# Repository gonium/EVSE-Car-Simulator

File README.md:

# EVSE-Car-Simulator

A simple car simulator PCB for testing EVSE, implements DIN EN 61851 and
J1772. This repository contains:

1. The hardware design files (KICAD)
2. The documentation for the car simulator.

Please see [https://evsim.gonium.net](https://evsim.gonium.net) for more
information.

# License

This project is (c) 2017 Mathias Dalheimer and available under the MIT
license. In short:

Permissions:
* Commercial use ok
* Modification ok
* Distribution ok
* Private use ok

Limitations:
* no liability
* no warranty

Conditions:
* keep license and copyright notice

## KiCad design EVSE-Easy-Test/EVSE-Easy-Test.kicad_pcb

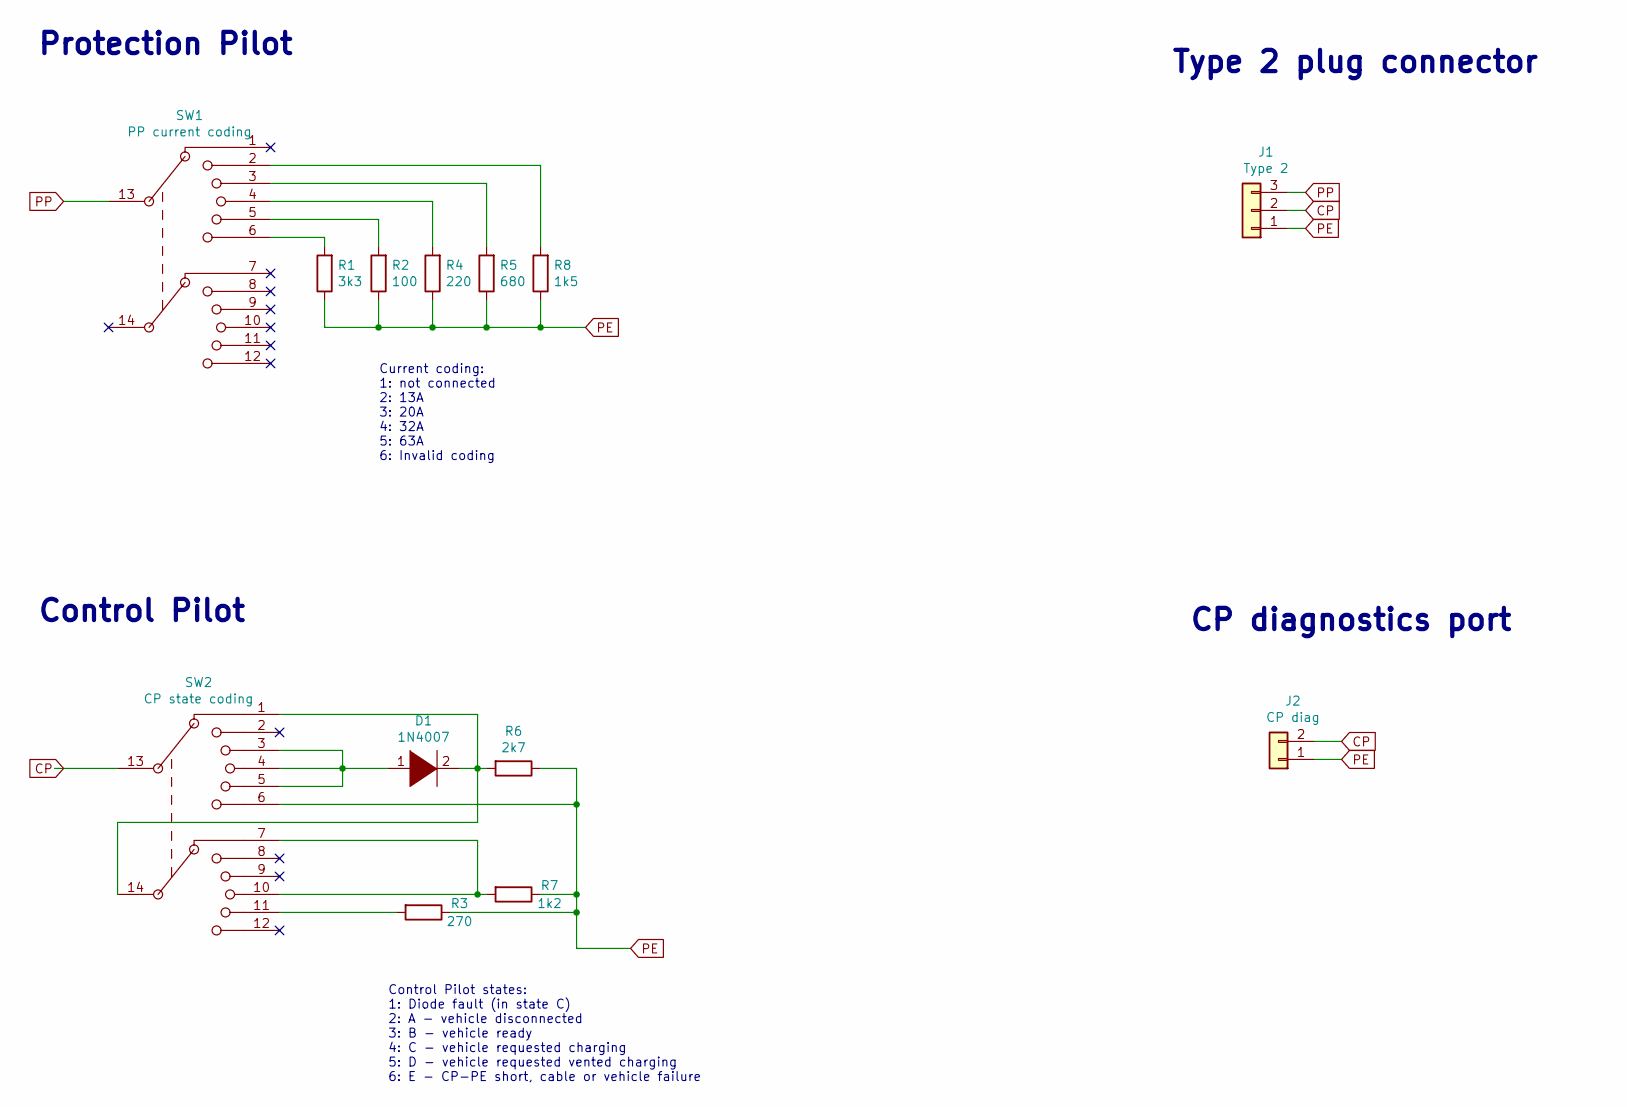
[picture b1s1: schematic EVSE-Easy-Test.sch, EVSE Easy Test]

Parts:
D1: 1N4007; D_DO-41_SOD81_P7.62mm_Horizontal
J1: Type 2; RIACon175_3poles_AKL175-03
J2: CP diag; Pin_Header_Straight_1x02_Pitch2.54mm
R1: 3k3; R_Axial_DIN0204_L3.6mm_D1.6mm_P7.62mm_Horizontal
R2: 100; R_Axial_DIN0204_L3.6mm_D1.6mm_P7.62mm_Horizontal
R3: 270; R_Axial_DIN0204_L3.6mm_D1.6mm_P7.62mm_Horizontal
R4: 220; R_Axial_DIN0204_L3.6mm_D1.6mm_P7.62mm_Horizontal
R5: 680; R_Axial_DIN0204_L3.6mm_D1.6mm_P7.62mm_Horizontal
R6: 2k7; R_Axial_DIN0204_L3.6mm_D1.6mm_P7.62mm_Horizontal
R7: 1k2; R_Axial_DIN0204_L3.6mm_D1.6mm_P7.62mm_Horizontal
R8: 1k5; R_Axial_DIN0204_L3.6mm_D1.6mm_P7.62mm_Horizontal
SW1: PP current coding; LorlinCK-1060
SW2: CP state coding; LorlinCK-1060

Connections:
CP: J1.2, J2.2, SW2.13
unnamed: D1.1 (K), SW2.3, SW2.4, SW2.5
unnamed: D1.2 (A), R6.2, SW2.1, SW2.14
unnamed: R1.2, SW1.6
unnamed: R2.2, SW1.5
unnamed: R3.2, SW2.11
unnamed: R4.2, SW1.4
unnamed: R5.2, SW1.3
unnamed: R7.2, SW2.7, SW2.10
unnamed: R8.2, SW1.2
PE: J1.1, J2.1, R1.1, R2.1, R3.1, R4.1, R5.1, R6.1, R7.1, R8.1, SW2.6
PP: J1.3, SW1.13

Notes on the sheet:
Current coding: 1: not connected 2: 13A 3: 20A 4: 32A 5: 63A 6: Invalid coding
Control Pilot states: 1: Diode fault (in state C) 2: A - vehicle disconnected 3: B - vehicle ready 4: C - vehicle requested charging 5: D - vehicle requested vented charging 6: E - CP-PE short, cable or vehicle failure
Type 2 plug connector
CP diagnostics port
Protection Pilot
Control Pilot

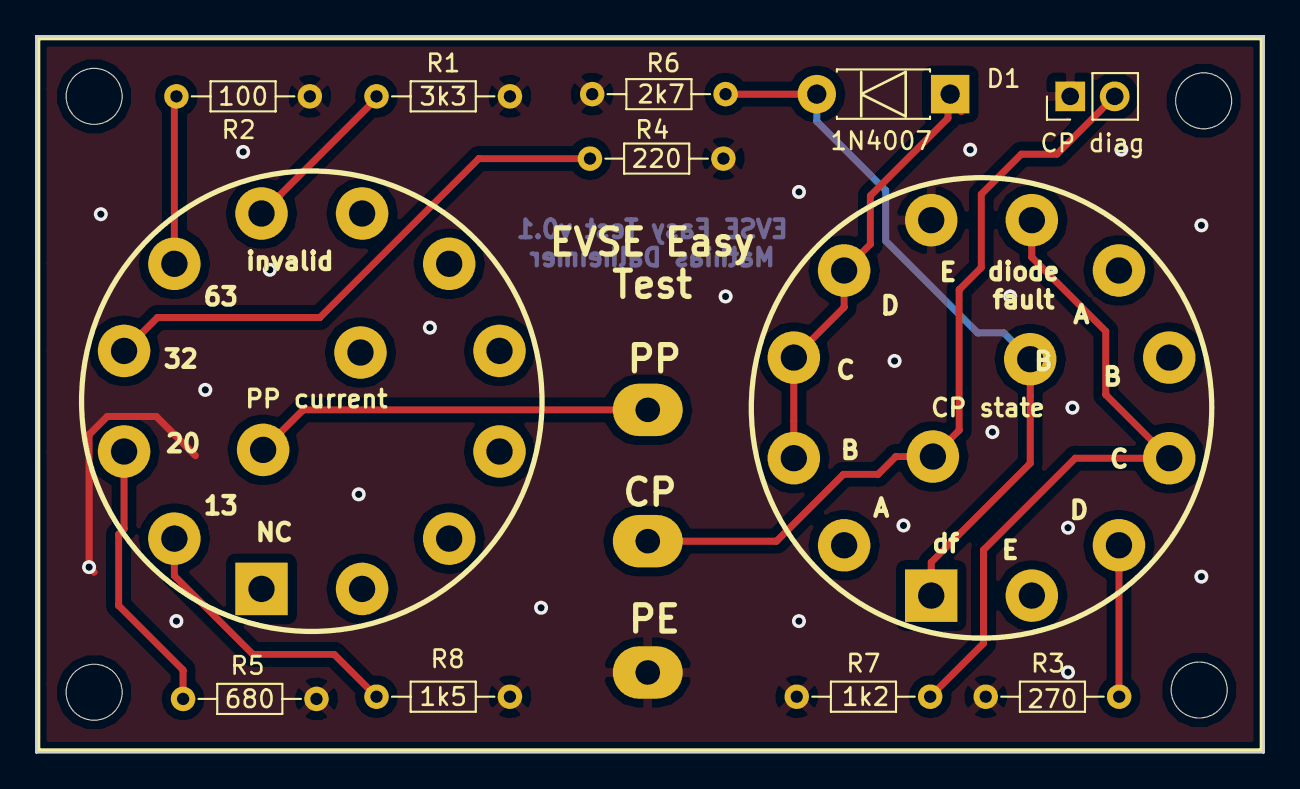
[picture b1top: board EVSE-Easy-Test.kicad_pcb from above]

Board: 2 copper layers, 70.1 x 40.9 mm, 13 parts (1 on the bottom side), 12 nets.

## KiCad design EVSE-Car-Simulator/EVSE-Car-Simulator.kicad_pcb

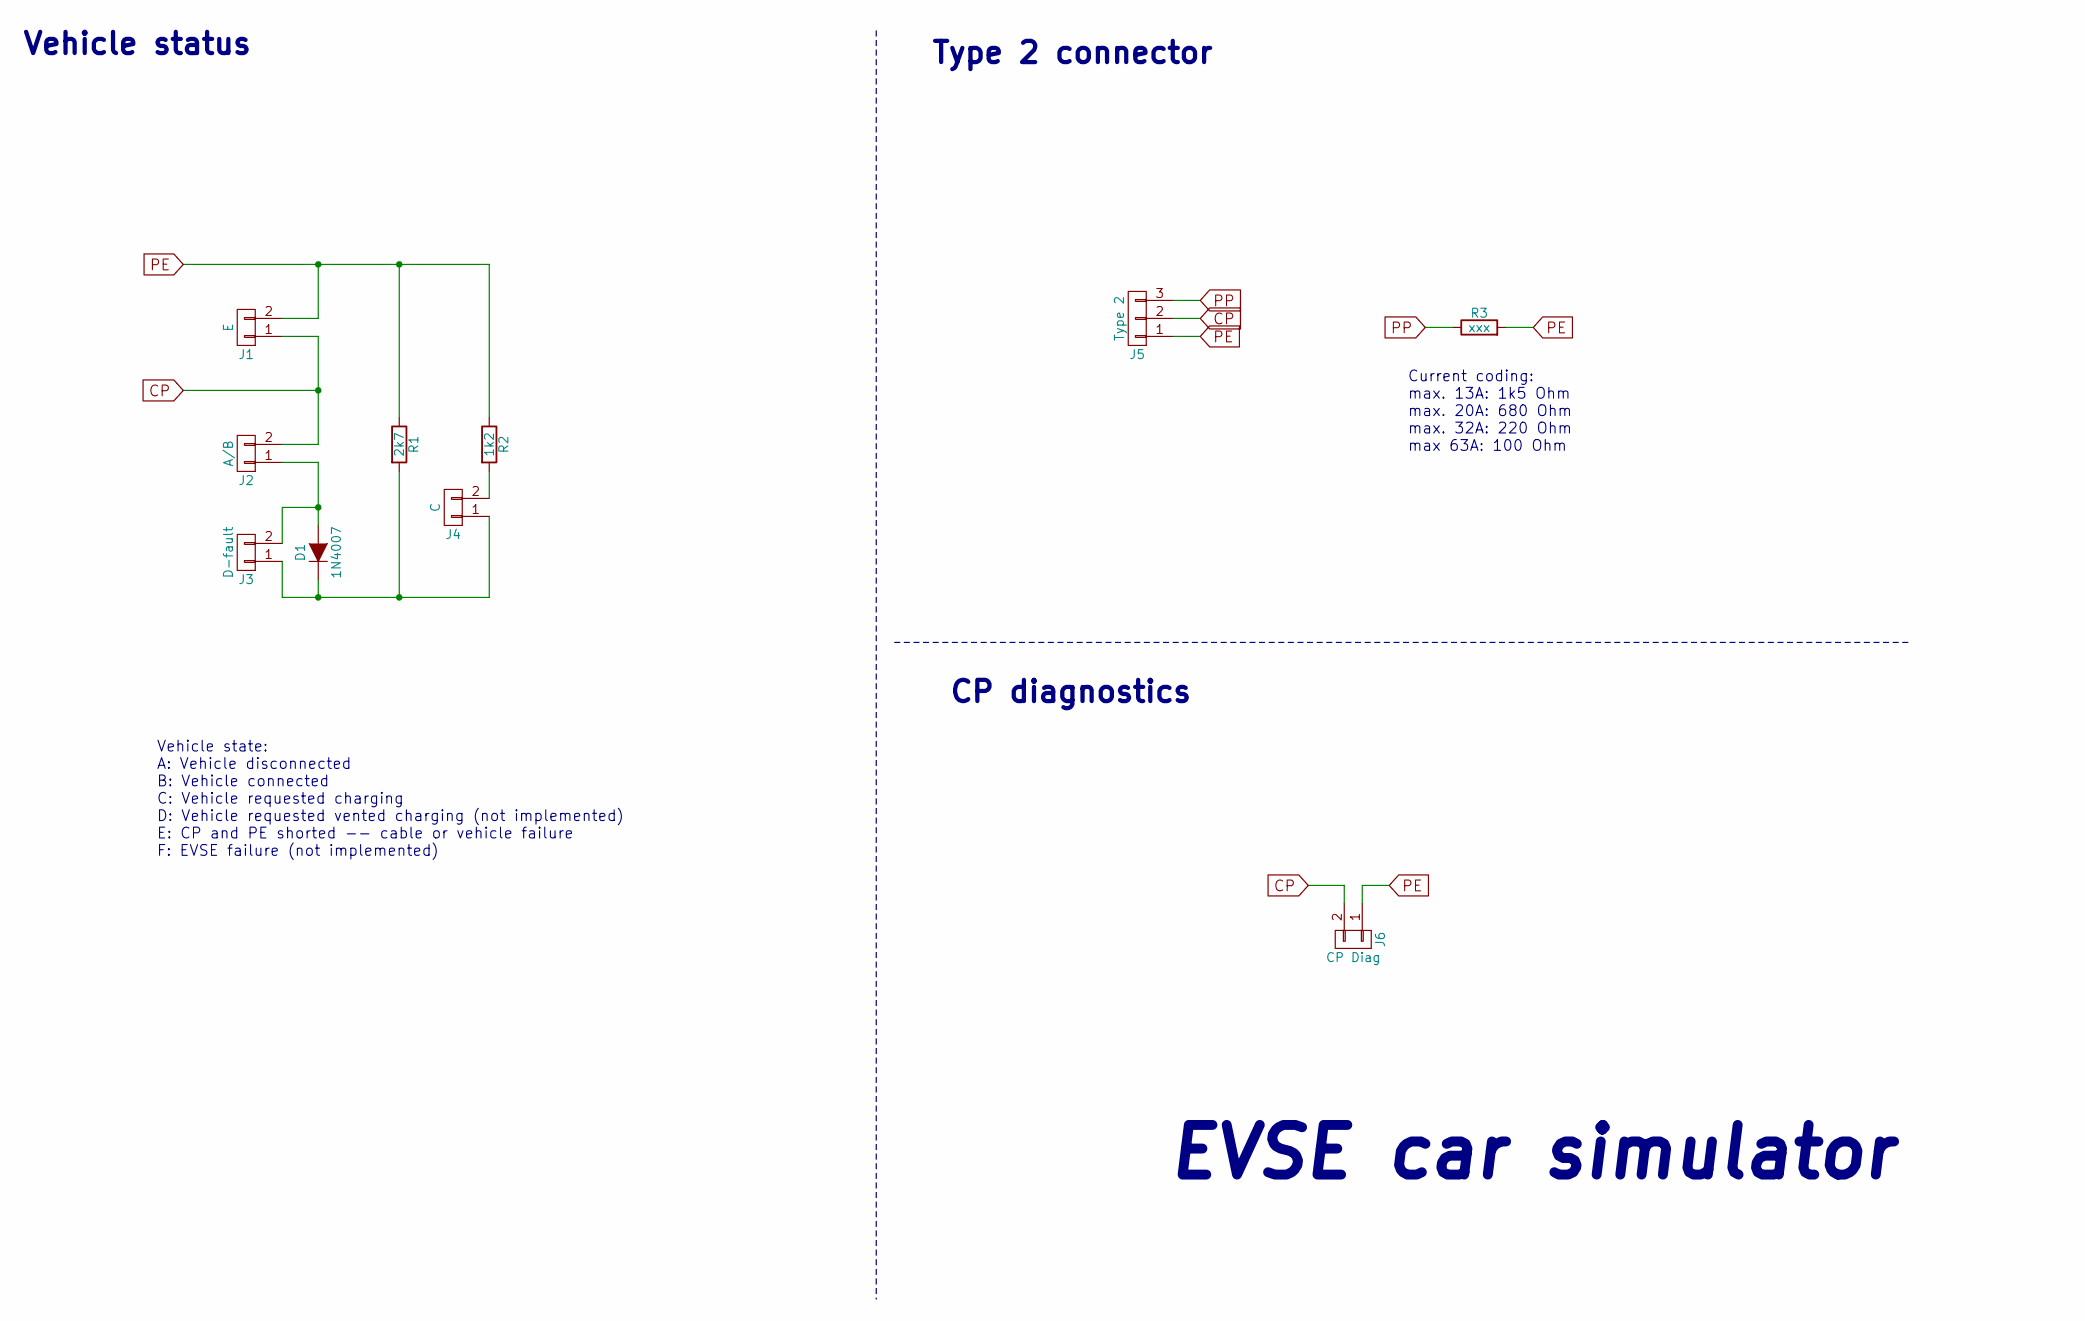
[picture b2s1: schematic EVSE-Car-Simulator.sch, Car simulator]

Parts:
D1: 1N4007; D_DO-41_SOD81_P7.62mm_Horizontal
J1: E; Pin_Header_Straight_1x02_Pitch2.54mm
J2: A/B; Pin_Header_Straight_1x02_Pitch2.54mm
J3: D-fault; Pin_Header_Straight_1x02_Pitch2.54mm
J4: C; Pin_Header_Straight_1x02_Pitch2.54mm
J5: Type 2; Type2-Solderpads
J6: CP Diag; Pin_Header_Straight_1x02_Pitch2.54mm
R1: 2k7; R_Axial_DIN0204_L3.6mm_D1.6mm_P7.62mm_Horizontal
R2: 1k2; R_Axial_DIN0204_L3.6mm_D1.6mm_P7.62mm_Horizontal
R3: xxx; R_Axial_DIN0204_L3.6mm_D1.6mm_P7.62mm_Horizontal

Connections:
CP: J1.1, J2.2, J5.2, J6.2
unnamed: D1.1 (K), J3.1, J4.1, R1.2
unnamed: D1.2 (A), J2.1, J3.2
unnamed: J4.2, R2.2
PE: J1.2, J5.1, J6.1, R1.1, R2.1, R3.2
PP: J5.3, R3.1

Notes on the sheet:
Current coding: max. 13A: 1k5 Ohm max. 20A: 680 Ohm max. 32A: 220 Ohm max 63A: 100 Ohm
Type 2 connector
Vehicle status
CP diagnostics
EVSE car simulator
Vehicle state: A: Vehicle disconnected B: Vehicle connected C: Vehicle requested charging D: Vehicle requested vented charging (not implemented) E: CP and PE shorted -- cable or vehicle failure F: EVSE failure (not implemented)

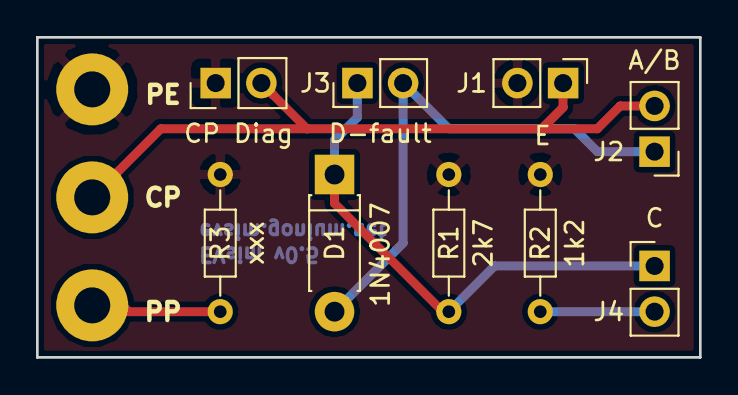
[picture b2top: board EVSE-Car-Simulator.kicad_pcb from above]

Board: 2 copper layers, 36.8 x 17.8 mm, 10 parts (0 on the bottom side), 6 nets.

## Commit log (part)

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2017-09-01 initial sketch, routing almost complete
2017-09-02 completely routed, gerber files for production generated.
2017-09-03 build of basic documentation structure
2017-09-04 changed from ascidoc to markdown, html generation via CSS now beautiful.
2017-09-04 fiddling with CSS, text grows.
2017-09-05 minor
2017-09-08 added images
2017-09-08 schematic missing
2017-09-08 enlarged
2017-09-08 texttexttext
2017-09-09 increased hole size for type2 connector, rerouted to make enough room
2017-09-09 text text
2017-09-09 text
2017-09-13 added picture of charging phases
2017-09-13 Text, mail links"
2017-09-13 added deployment target
2017-09-14 switched to html5 output, now renders correctly on mobile devices.
2017-09-14 added short readme
2017-09-14 short explanation of license added
2017-09-14 added dimensions of pcb
2017-09-14 moved old version to subdir
2017-09-14 gerbers for v0.2 generated
2017-09-15 hinweis frequenz
2017-09-18 simplified things, added TODOs for images
2017-09-18 added google analytics to track usage
2017-09-18 youtube-video embedded
2017-09-18 added images of pcbs
2017-10-03 upgraded images to show v0.2 (black pcb)
2017-10-10 added duty cycle explanation
2017-10-10 wording
2017-10-15 note on how to report bugs
2017-10-15 new todo: how to test a wallbox
2017-10-15 typo
2017-10-21 added drill template for bopla et215 housing
2017-10-22 pic of second simulator added
2017-10-22 price 6 Euro
2017-10-22 added pc socket
2017-10-23 prüfverfahren dokumentiert, neue bilder
2017-10-24 Verweis auf DIN 61851 eingefügt
2017-10-24 cleanup
2017-10-24 added keywords/description header, cleaned up header order
2017-10-24 adjusted font size for printing
2017-11-03 widerstandswerte richtig herum getauscht;
2017-11-03 included development server
2017-11-05 bestellung beschrieben und aktualisiert
2017-11-09 abschnitt testen überarbeitet
2017-11-09 proper development mode with automatic reload
2017-11-10 layout
2017-11-13 preis angepasst
2017-11-13 kleinigkeiten
2017-11-14 more keywords
2017-11-16 beschreibung wohnwagenadapter
2017-11-16 link auf pruefung
2017-11-16 ZOE technische Mindestvoraussetzungen
2017-11-24 link auf zoe ladevoraussetzungen
2017-11-29 image cee-adaptor added
2017-12-11 start of english version
2018-01-14 made devmode executable
2018-01-14 changed connector of test lines
2018-01-14 CP Diag connector, closes #3
2018-01-15 hint: class 2 toggle switches, closes #2
2018-01-26 v0.3 dokumentiert, bild geändert, reichelt-bestellliste integriert
2018-01-29 configured ebook build
2018-02-11 anmerkungen bestellliste, sicherungswerte
2018-02-11 price
2018-02-11 clarification of order procedure
2018-02-21 Name entfernt
2018-04-29 Pricing, commented out unverified parts list
2018-04-29 Correction: Switched J2 <-> J4 in adapter description (sec. 4.3)
2018-05-27 VG Wort counter added
2018-06-07 deactivated google analytics
2018-06-10 Typo, cable rejection
2018-07-23 away notice
2018-11-26 converted to kicad 5
2018-11-26 updated schematic to reflect A/B/C/D/E states properly
2018-11-26 Schematic exported to PDF
2018-11-26 saved
2018-11-30 Added schematic and footprints of new version
2018-11-30 archived footprints into project library
2018-12-03 initial layout
2018-12-04 completed and sent to aisler
2018-12-04 now with real edge cuts! now really ordered at aisler.net!
2018-12-04 final (?!?) changes to aisler.net order.
2018-12-14 added production files for v0.5
2018-12-22 second prototype as ordered
2019-01-02 R8 adjusted, some alignments
2019-01-03 template for easy test created
2019-01-03 reworking documentation
2019-01-03 extracted CP function schematic
2019-01-03 update of documentation to v0.5 complete
2019-03-05 added TIKZ sticker design
2019-03-05 rounded corners
2019-03-07 Added 2x2nuped version, fiddled around
2019-03-20 Implemented full clean target (now cleans like mr. proper)
2019-03-20 first prototype complete
2019-04-02 adjusted PE and L1 labels
2019-04-02 sectors instead of lines
2019-04-04 renamed sticker for BOPLA ET-215; introduced generic threephase sticker, Makefile cleaned
2019-04-04 moving stuff around
2019-10-19 formatting
2019-10-19 Hinweis weitere Bauteile lohnen nicht
2019-12-01 New Housing: BOTPLA ET 220
2023-02-02 updated price
2023-02-05 preisanpassung
